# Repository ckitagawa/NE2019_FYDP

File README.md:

# NE2019_FYDP
Fiber Optic Tactile/Pressure Sensor: Nanotechonology Engineering Fourth Year Design Project 2019

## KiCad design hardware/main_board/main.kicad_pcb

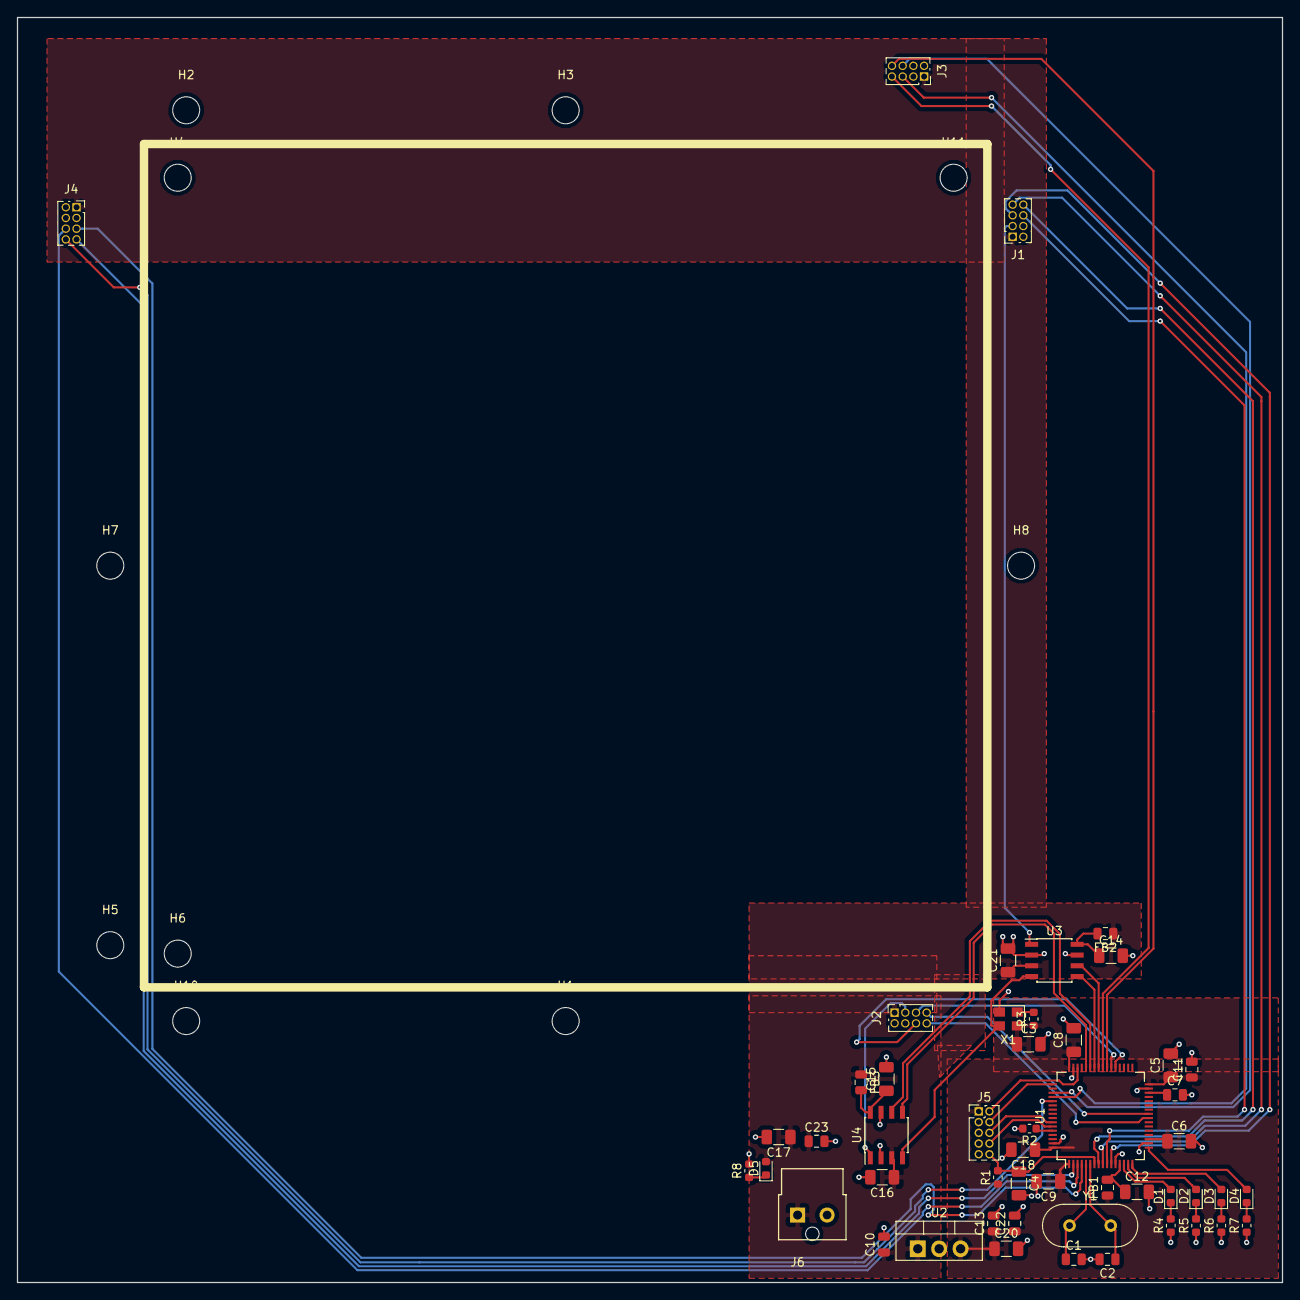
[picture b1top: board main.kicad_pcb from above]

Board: 2 copper layers, 150.0 x 150.0 mm, 60 parts (0 on the bottom side), 48 nets.

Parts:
C1, C2: 30 pF; C_0805_2012Metric
C3, C4, C5, C6, C8, C9, C12, C14, C15, C16, C17, C18, C20, C21: 100 nF; C_1206_3216Metric
C7, C11, C22, C23: 4.7 uF; C_0805_2012Metric
C10, C13: 1 uF; C_0805_2012Metric
D1: Green; LED_0603_1608Metric
D2: Red; LED_0603_1608Metric
D3, D4: Yellow; LED_0603_1608Metric
D5: LED; LED_0603_1608Metric
FB1, FB2, FB3: Ferrite_Bead; L_0805_2012Metric
H1, H2, H3, H4, H5, H6, H7, H8, H10, H11: MountingHole; MountingHole_3.2mm_M3
J1, J2, J3, J4: Conn_02x04_Counter_Clockwise; PinSocket_2x04_P1.27mm_Vertical
J5: Conn_02x05_Odd_Even; PinHeader_2x05_P1.27mm_Vertical
J6: Conn_01x02_Female; Ultra-Fit 2 Pin 3.5 mm
R1: 100k; R_0603_1608Metric
R2: 510; R_0603_1608Metric
R3: 10k; R_0603_1608Metric
R4, R5, R6, R7, R8: 180; R_0603_1608Metric
U1: STM32F410RBTx; LQFP-64_10x10mm_P0.5mm
U2: SPX1117M3-L-3-3/TR; TO-220-3_Vertical
U3, U4: ADS1252; SOIC-8_3.9x4.9mm_P1.27mm
X1: ECS-2333; Oscillator_SMD_Abracon_ASE-4Pin_3.2x2.5mm
Y1: 16 MHz; Crystal_HC49-U_Vertical

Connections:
+3V3: C3.1, C5.1, C6.1, C8.1, C9.1, C11.1, C13.1, C18.1, C20.1, C22.1, FB1.1, J5.1, R1.1, R3.1, U1.1, U1.19, U1.32, U1.48, U1.64, U2.3, X1.4
+5V: C10.1, C16.1, C17.1, C21.1, C23.1, D5.2, FB2.1, FB3.1, J1.1, J2.1, J3.1, J4.1, J6.1, U2.1, U3.3, U4.3
DATA1: U1.42, U3.5
DATA2: U1.44, U4.5
GND: C1.2, C2.2, C3.2, C4.2, C5.2, C6.2, C7.2, C8.2, C9.2, C10.2, C11.2, C12.2, C13.2, C14.2, C15.2, C16.2, C17.2, C18.2, C20.2, C21.2, C22.2, C23.2, J1.2, J1.4, J2.2, J2.4, J3.2, J3.3, J3.4, J4.2, J4.3, J4.4, J5.3, J5.5, J6.2, R2.2, R4.1, R5.1, R6.1, R7.1, R8.2, U1.12, U1.18, U1.31, U1.47, U1.63, U2.2, U3.2, U3.7, U4.2, U4.7, X1.2
IN1: J1.3, U3.1
IN2: J2.3, U4.1
NRST: C4.1, J5.10, R1.2, U1.7
unnamed: C7.1, U1.30
unnamed: C12.1, FB1.2, U1.13
unnamed: C14.1, FB2.2, U3.8
unnamed: C15.1, FB3.2, U4.8
unnamed: D1.1, R4.2
unnamed: D2.1, R5.2
unnamed: D3.1, R6.2
unnamed: D4.1, R7.2
unnamed: D5.1, R8.1
unnamed: J1.5, U1.11
unnamed: J1.6, U1.10
unnamed: J1.7, U1.9
unnamed: J1.8, U1.8
unnamed: J2.5, U1.38
unnamed: J2.6, U1.37
unnamed: J2.7, U1.25
unnamed: J2.8, U1.24
unnamed: J3.5, U1.52
unnamed: J3.6, U1.51
unnamed: J3.7, U1.40
unnamed: J3.8, U1.39
unnamed: J4.5, U1.4
unnamed: J4.6, U1.3
unnamed: J4.7, U1.2
unnamed: J4.8, U1.53
unnamed: R2.1, U1.60
unnamed: R3.2, X1.1
unnamed: U3.4, U4.4, X1.3
OSC_IN: C1.1, U1.5, Y1.1
OSC_OUT: C2.1, U1.6, Y1.2
PA0: D1.2, U1.14
PA1: D2.2, U1.15
PA2: D3.2, U1.16
PA3: D4.2, U1.17
SCLK1: U1.41, U3.6
SCLK2: U1.43, U4.6
SWCLK: J5.4, U1.49
SWDIO: J5.2, U1.46
USART1_RX: J5.8, U1.59
USART1_TX: J5.6, U1.58

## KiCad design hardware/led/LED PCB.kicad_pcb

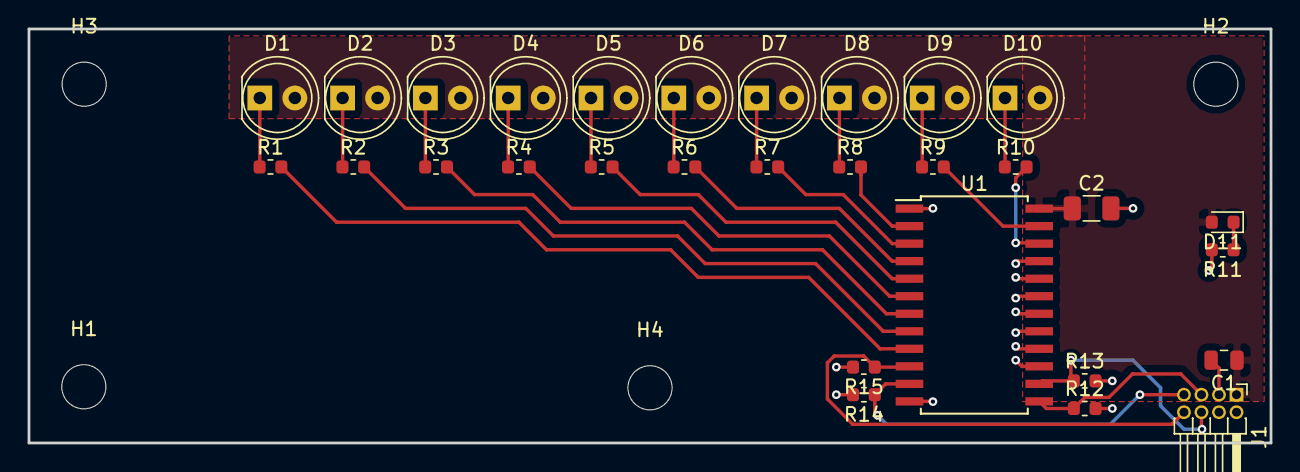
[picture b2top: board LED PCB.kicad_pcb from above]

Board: 2 copper layers, 90.0 x 30.0 mm, 34 parts (0 on the bottom side), 27 nets.

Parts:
C1: 4.7 uF; C_0805_2012Metric
C2: 100 nF; C_1206_3216Metric
D1, D2, D3, D4, D5, D6, D7, D8, D9, D10: LED; LED_D5.0mm_Clear
D11: LED; LED_0603_1608Metric
H1, H2, H3, H4: MountingHole; MountingHole_3.2mm_M3
J1: Conn_02x04_Counter_Clockwise; PinHeader_2x04_P1.27mm_Horizontal
R1, R2, R3, R4, R5, R6, R7, R8, R9, R10: 125; R_0603_1608Metric
R11: 180; R_0603_1608Metric
R12, R13, R14, R15: 10k; R_0603_1608Metric
U1: CD74HC4067M; SOIC-24W_7.5x15.4mm_P1.27mm

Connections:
+5V: C1.1, C2.1, D1.2, D2.2, D3.2, D4.2, D5.2, D6.2, D7.2, D8.2, D9.2, D10.2, D11.2, J1.1, U1.24
GND: C1.2, C2.2, J1.2, J1.3, J1.4, R11.2, R12.2, R13.2, R14.2, R15.2, U1.1, U1.12, U1.15, U1.16, U1.17, U1.18, U1.19, U1.20, U1.21
unnamed: D1.1, R1.1
unnamed: D2.1, R2.1
unnamed: D3.1, R3.1
unnamed: D4.1, R4.1
unnamed: D5.1, R5.1
unnamed: D6.1, R6.1
unnamed: D7.1, R7.1
unnamed: D8.1, R8.1
unnamed: D9.1, R9.1
unnamed: D10.1, R10.1
unnamed: D11.1, R11.1
unnamed: R1.2, U1.9
unnamed: R2.2, U1.8
unnamed: R3.2, U1.7
unnamed: R4.2, U1.6
unnamed: R5.2, U1.5
unnamed: R6.2, U1.4
unnamed: R7.2, U1.3
unnamed: R8.2, U1.2
unnamed: R9.2, U1.23
unnamed: R10.2, U1.22
S0: J1.8, R15.1, U1.10
S1: J1.7, R14.1, U1.11
S2: J1.6, R13.1, U1.14
S3: J1.5, R12.1, U1.13

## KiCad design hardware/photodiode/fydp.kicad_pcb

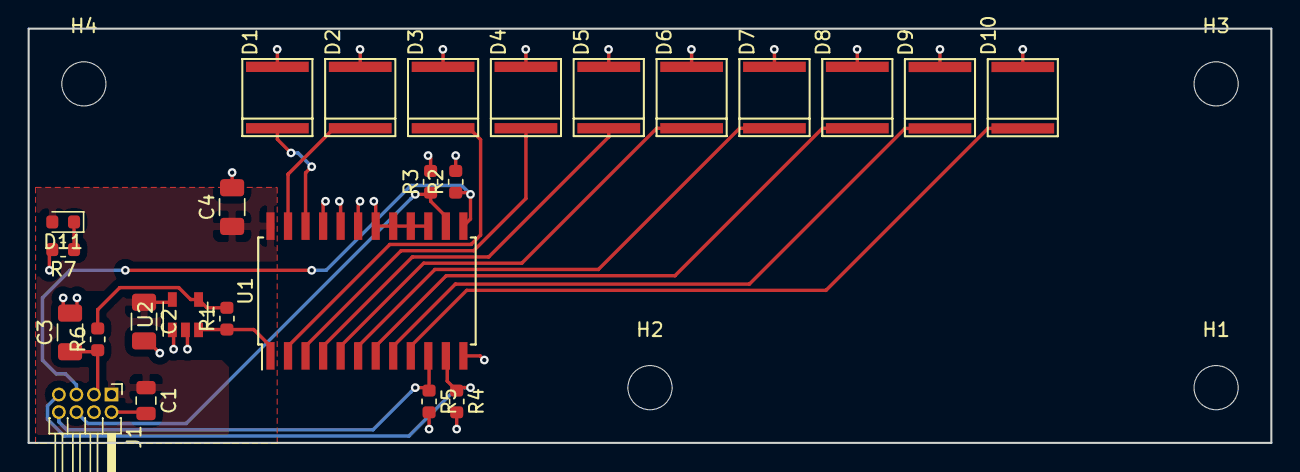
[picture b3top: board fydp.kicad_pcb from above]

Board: 2 copper layers, 90.0 x 30.0 mm, 29 parts (0 on the bottom side), 20 nets.

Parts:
C1: 4.7 uF; C_0805_2012Metric
C2, C4: 100 nF; C_1206_3216Metric
C3: 47 nF; C_1206_3216Metric
D1, D2, D3, D4, D5, D6, D7, D8, D9, D10: D_Photo; PDB-C171SM
D11: LED; LED_0603_1608Metric
H1, H2, H3, H4: MountingHole; MountingHole_3.2mm_M3
J1: Conn_02x04_Counter_Clockwise; PinHeader_2x04_P1.27mm_Horizontal
R1: 1.5M; R_0603_1608Metric
R2, R3, R4, R5: 10k; R_0603_1608Metric
R6: 800; R_0603_1608Metric
R7: 180; R_0603_1608Metric
U1: CD74HC4067M; SOIC-24W_7.5x15.4mm_P1.27mm
U2: LM321; SOT-23-5

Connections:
+5V: C1.1, C2.1, C4.1, D11.2, J1.1, U1.24, U2.5
COM: R1.1, U1.1, U2.3
GND: C1.2, C2.2, C3.2, C4.2, D1.2, D2.2, D3.2, D4.2, D5.2, D6.2, D7.2, D8.2, D9.2, D10.2, J1.2, J1.4, R2.2, R3.2, R4.2, R5.2, R7.2, U1.12, U1.15, U1.16, U1.17, U1.18, U1.19, U1.20, U1.21, U2.1, U2.2
unnamed: D1.1, U1.22
unnamed: D2.1, U1.23
unnamed: D3.1, U1.2
unnamed: D4.1, U1.3
unnamed: D5.1, U1.4
unnamed: D6.1, U1.5
unnamed: D7.1, U1.6
unnamed: D8.1, U1.7
unnamed: D9.1, U1.8
unnamed: D10.1, U1.9
unnamed: D11.1, R7.1
unnamed: R1.2, R6.2, U2.4
PD_out: C3.1, J1.3, R6.1
S0: J1.8, R5.1, U1.10
S1: J1.7, R4.1, U1.11
S2: J1.6, R3.1, U1.14
S3: J1.5, R2.1, U1.13

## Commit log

2019-02-24 00 - Initial Commit
2019-02-24 01 - Add licensce and gitignore
2019-02-24 02 - Add hardware (KiCad) and start of UI code
2019-02-24 Update LICENSE
2019-02-25 03 - Add base UI code
2019-02-26 04 - Fix NVIC Controller
2019-02-26 05 - Implement rough main loop
2019-02-26 06 - Update python parser
2019-03-01 07 - Improve python script and fix ADC (slight instability)
2019-03-01 Create gui.py
    The gui code.
2019-03-02 08 - Fix up GUI
2019-03-03 09 - Improve device readings and streamline output.
2019-03-05 10 - Fix pinout, ui render and timing
2019-03-05 11 - Fix calibration routine
2019-03-18 Polyfit noise removal, fft graph, colour bar temp fix, graphical debugging
2019-03-18 12 - Improve read speed
2019-03-18 14 - Get data
